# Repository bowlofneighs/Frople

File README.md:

# frople
Frople is a split ergonomic keyboard with a 40 key layout. It utilizes a 6x3 main matrix and a 2x1 thumbfan on each side. It uses 2 Arduino Pro Micros as its MCUs and QMK for the firmware. The keys were designed specifically with my hand dimensions in mind, seeing as I took measurements of my finger-length to decide the key stagger. It will take advantage of home-row-mods to allow me to still use my mod keys with such a small key footprint. It also has extra layers to account for the keys that could not fit on the main layer. It uses a TRS cable to communicate between the two halves of the keyboard using serial communcation. In the future it could theoretically be upgraded with a Nice!Nano V2 to allow for wireless communication between the two halves and the computer through BLE (bluetooth low energy). However my current computer does not have bluetooth and the Nice!Nano V2 was more expensive than the Arduino Pro Micro and as such I went with the Pro Micro for the MCU.

I built Frople because I have always been interested by those desktop setup videos, they seemed really cool, and I thought that a split keyboard would be a way to take my desk to the next level. I also made it because I tried out home-row-mods on my normal keyboard using a software called [Kanata](https://github.com/jtroo/kanata) and I found that it really increased my power-useriness and I wanted to take that to the next level. I also am really unsatisfied with my current keyboard, especially the lack of linux compatibal firmware. The final reason I wanted to make a split keyboard is because it sounded like a really fun project to get into hardware design with.

|Item                  |Description                  |Quantity                          |Unit Price CAD   |Unit Price USD|Price + tax * quantity (CAD)|Price + tax * quantity (USD)|Shipping CAD             |shipping USD|Note                                                  |Link                                                                                                                                                                                                                                                                                                                                                                                                                                                                                                                                                                                    |
|----------------------|-----------------------------|----------------------------------|-----------------|--------------|----------------------------|----------------------------|-------------------------|------------|------------------------------------------------------|----------------------------------------------------------------------------------------------------------------------------------------------------------------------------------------------------------------------------------------------------------------------------------------------------------------------------------------------------------------------------------------------------------------------------------------------------------------------------------------------------------------------------------------------------------------------------------------|
|Red Choc Switches     |Key Switches                 |40pcs                             |29.41 + 3.82(tax)|23.93USD      |33.23                       |23.93 USD                   |FREE                     |FREE        |                                                      |https://www.aliexpress.com/item/1005008751312031.html?algo_exp_id=cdb82bfe-653e-4ba2-895b-58cb39c5a6ad-1&pdp_ext_f=%7B%22order%22%3A%22150%22%2C%22eval%22%3A%221%22%2C%22fromPage%22%3A%22search%22%7D&utparam-url=scene%3Asearch%7Cquery_from%3A%7Cx_object_id%3A1005008751312031%7C_p_origin_prod%3A                                                                                                                                                                                                                                                                                 |
|Kailh Hot Swap sockets|Hot swaps                    |1 (they come in packs of 100 :hs:)|12.87 + 1.67(tax)|10.47 USD     |14.54                       |10.47 USD                   |FREE                     |FREE        |even though it was 100 they were still the cheapest   |https://www.aliexpress.com/item/1005006625852715.html?algo_exp_id=faa48a85-e9cd-40e5-93a0-2959f27b83d9-4&pdp_ext_f=%7B%22order%22%3A%22105%22%2C%22spu_best_type%22%3A%22order%22%2C%22eval%22%3A%221%22%2C%22fromPage%22%3A%22search%22%7D&utparam-url=scene%3Asearch%7Cquery_from%3A%7Cx_object_id%3A1005006625852715%7C_p_origin_prod%3A                                                                                                                                                                                                                                             |
|Arduino Pro Micro     |MCU                          |2                                 |8.99 + 1.16      |7.31 USD      |20.3                        |14.62 USD                   |FREE                     |FREE        |                                                      |https://www.aliexpress.com/item/1005008804370504.html?aem_p4p_detail=202601150944273562095180064590002000670&algo_exp_id=7d831326-f6b0-4daf-bc1d-06556968d806-7&pdp_ext_f=%7B%22order%22%3A%2229%22%2C%22eval%22%3A%221%22%2C%22fromPage%22%3A%22search%22%7D&utparam-url=scene%3Asearch%7Cquery_from%3A%7Cx_object_id%3A1005008804370504%7C_p_origin_prod%3A&search_p4p_id=202601150944273562095180064590002000670_2                                                                                                                                                                   |
|Keycaps               |choc low profile ldsa keycaps|4 they come in packs of 10        |5 + 0.65         |4.06 USD      |22.6                        |16.27 USD                   |10 + 1.3                 |8.13USD     |I couldn’t find cheaper unmarked keycaps on aliexpress|https://lowprokb.ca/collections/keycaps/products/ldsa-low-profile-blank-keycaps?variant=44790995878052                                                                                                                                                                                                                                                                                                                                                                                                                                                                                  |
|SJ1-3533NG            |TRS audio jack               |2                                 |3.15 + 0.40      |2.55 USD      |7.1                         |5.11 USD                    |5.54 + 0.72              |4.50 USD    |LCSC was much more expensive bc shipping              |https://www.aliexpress.com/item/1005007818050385.html?spm=a2g0o.productlist.main.2.428d1a0el9FCCd&algo_pvid=9e128295-691e-43e5-8a00-b08dc531eca2&algo_exp_id=9e128295-691e-43e5-8a00-b08dc531eca2-1&pdp_ext_f={%22order%22%3A%221%22%2C%22eval%22%3A%221%22%2C%22fromPage%22%3A%22search%22}&pdp_npi=6%40dis!CAD!3.15!3.15!!!15.45!15.45!%402101c44517685003345927398e8be0!12000042315760823!sea!CA!0!ABX!1!0!n_tag%3A-29910%3Bd%3A53760023%3Bm03_new_user%3A-29895&curPageLogUid=4tlGIj6PnRZU&utparam-url=scene%3Asearch&#124;query_from%3A&#124;x_object_id%3A1005007818050385&#124;_p_origin_prod%3A|
|PCB                   |keyboard pcb                 |1                                 |                 |19.00 USD     |                            |19.00 USD                   |                         |13.25 USD   |                                                      |https://hc-cdn.hel1.your-objectstorage.com/s/v3/6d1642395864fce0_image.png                                                                                                                                                                                                                                                                                                                                                                                                                                                                                                              |
|ec-11                 |rotary encoder               |1 They come in packs of 5         |1.62 + 0.21      |1.31 USD      |1.83                        |1.31 USD                    |FREE                     |FREE        |                                                      |https://www.aliexpress.com/item/1005003824684681.html?algo_exp_id=11db7878-987f-4212-a431-20684286fbad-2&pdp_ext_f=%7B%22order%22%3A%22289%22%2C%22spu_best_type%22%3A%22order%22%2C%22eval%22%3A%221%22%2C%22fromPage%22%3A%22search%22%7D&utparam-url=scene%3Asearch%7Cquery_from%3A%7Cx_object_id%3A1005003824684681%7C_p_origin_prod%3A                                                                                                                                                                                                                                             |
|                      |                             |                                  |                 |              |                            |                            |                         |            |                                                      |                                                                                                                                                                                                                                                                                                                                                                                                                                                                                                                                                                                        |
|Total                 |                             |                                  |                 |              |99.6 CAD (not including pcb)|90.71 USD                   |17.56 (Not including pcb)|25.88       |full cost:: 116.59 USD                                |                                                                                                                                                                                                                                                                                                                                                                                                                                                                                                                                                                                        |

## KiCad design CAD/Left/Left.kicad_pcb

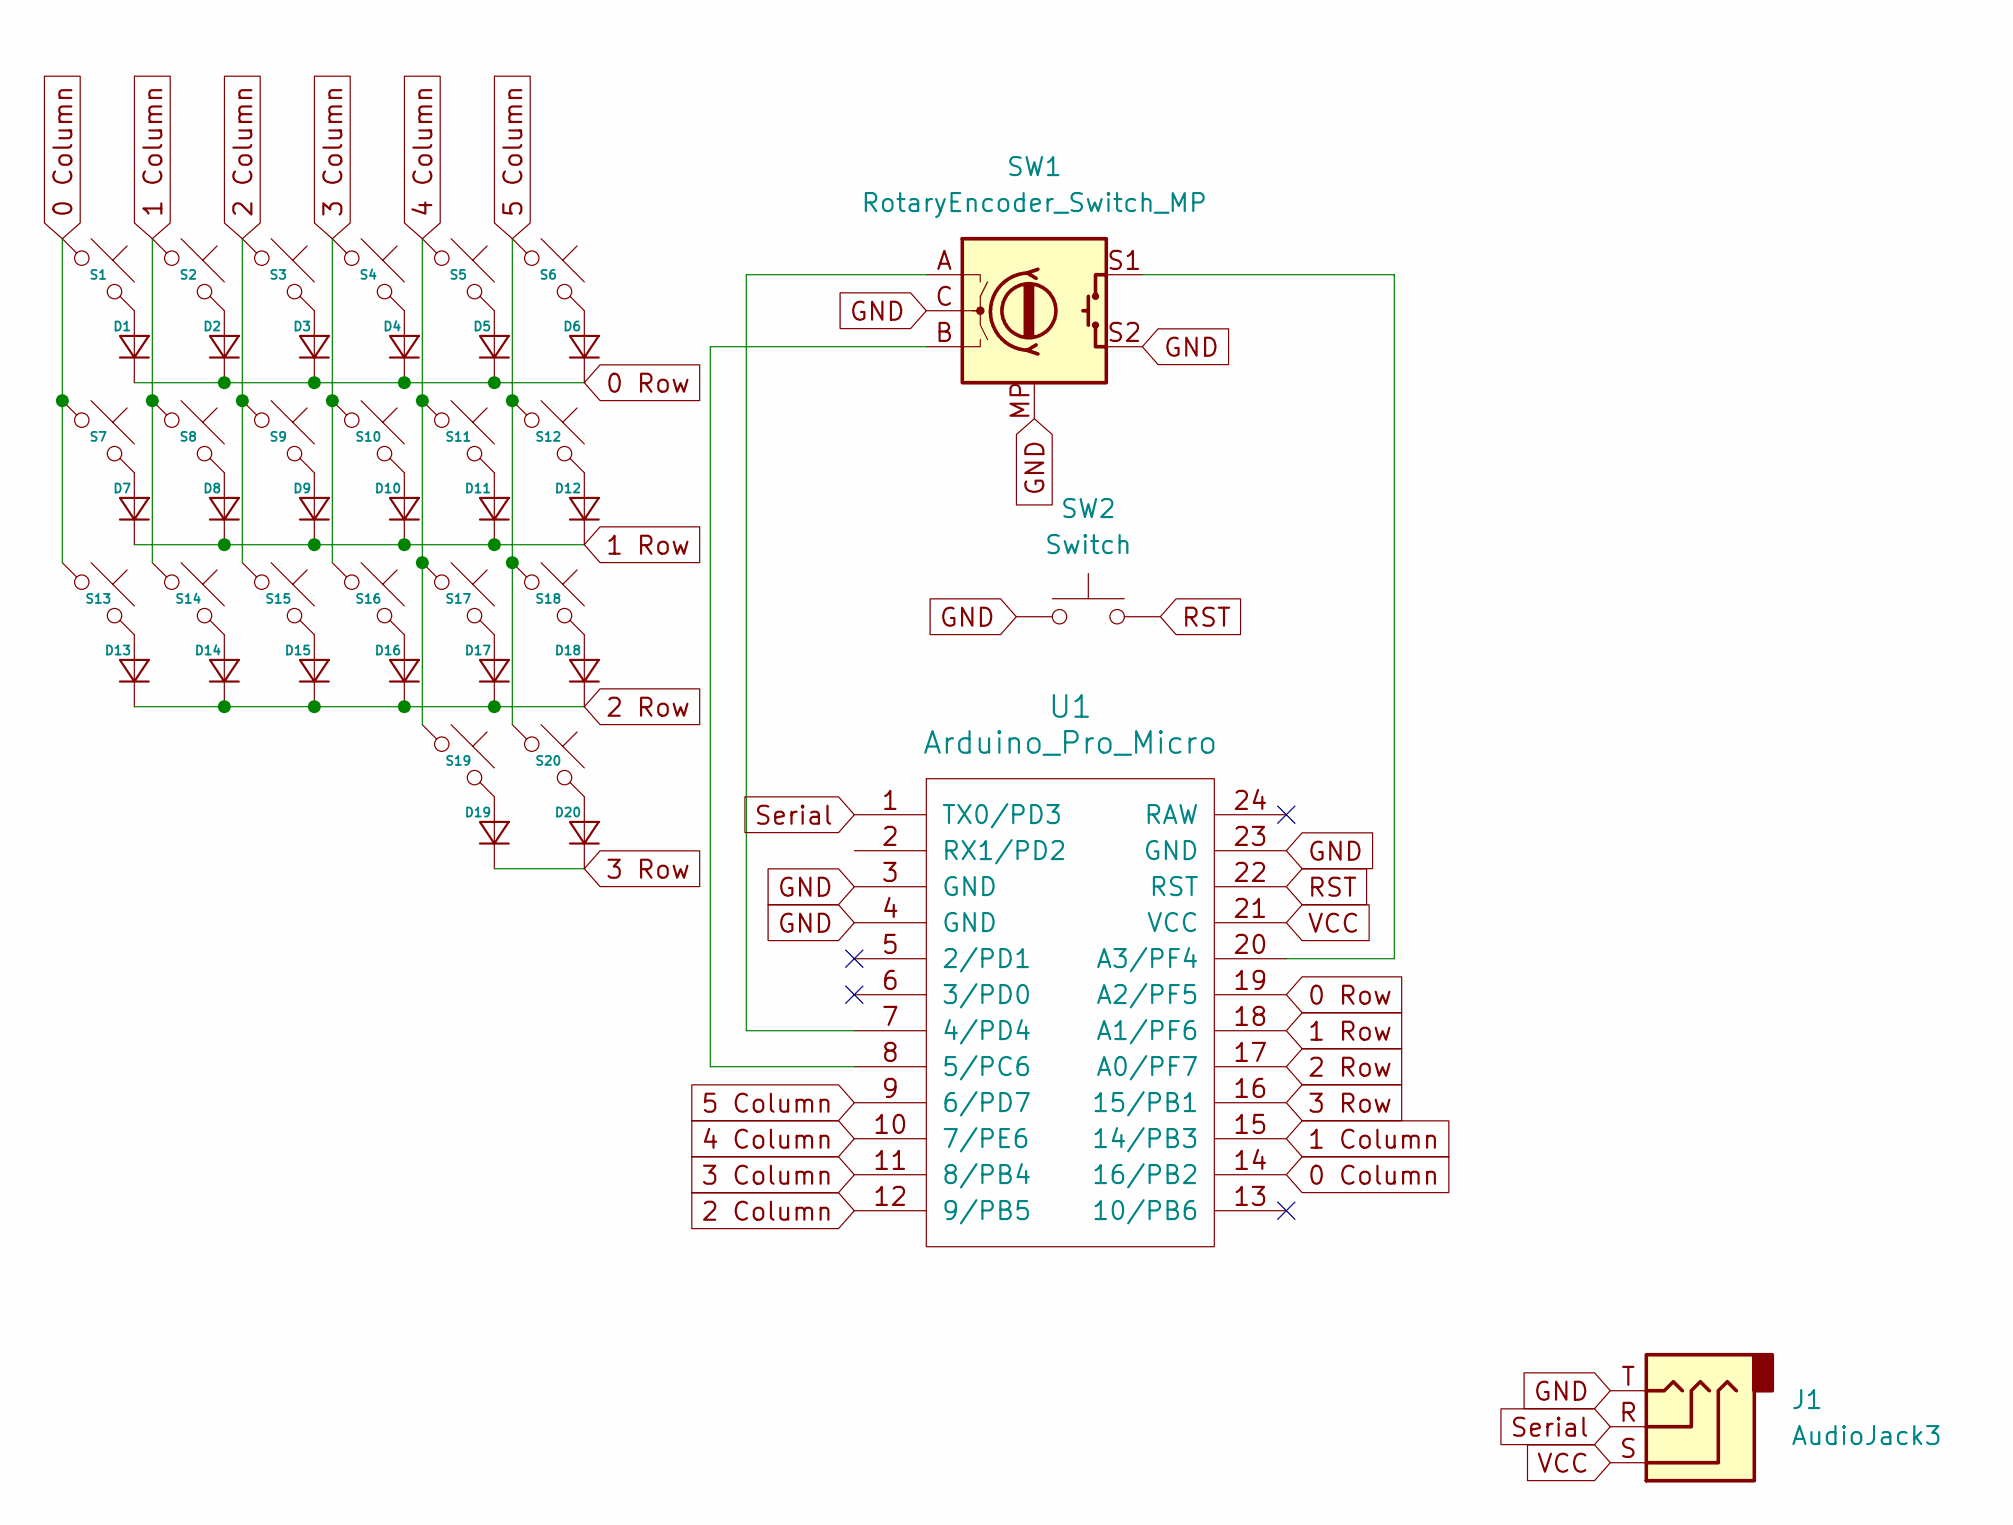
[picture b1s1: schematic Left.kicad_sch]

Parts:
D1, D2, D3, D4, D5, D6, D7, D8, D9, D10, D11, D12, D13, D14, D15, D16, D17, D18, D19, D20: D_SOD-123
J1: AudioJack3; Jack_3.5mm_CUI_SJ1-3533NG_Horizontal_CircularHoles
S1, S2, S3, S4, S5, S6, S7, S8, S9, S10, S11, S12, S13, S14, S15, S16, S17, S18, S19, S20: Hotswap_Choc_V1
SW1: RotaryEncoder_Switch_MP; RotaryEncoder_Alps_EC11E-Switch_Vertical_H20mm
SW2: Switch; Button_MJTP1243
U1: Arduino_Pro_Micro; Sparkfun_Pro_Micro

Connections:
0 Column: S1.1, S7.1, S13.1, U1.14 (16/PB2)
0 Row: D1.1 (K), D2.1 (K), D3.1 (K), D4.1 (K), D5.1 (K), D6.1 (K), U1.19 (A2/PF5)
1 Column: S2.1, S8.1, S14.1, U1.15 (14/PB3)
1 Row: D7.1 (K), D8.1 (K), D9.1 (K), D10.1 (K), D11.1 (K), D12.1 (K), U1.18 (A1/PF6)
2 Column: S3.1, S9.1, S15.1, U1.12 (9/PB5)
2 Row: D13.1 (K), D14.1 (K), D15.1 (K), D16.1 (K), D17.1 (K), D18.1 (K), U1.17 (A0/PF7)
3 Column: S4.1, S10.1, S16.1, U1.11 (8/PB4)
3 Row: D19.1 (K), D20.1 (K), U1.16 (15/PB1)
4 Column: S5.1, S11.1, S17.1, S19.1, U1.10 (7/PE6)
5 Column: S6.1, S12.1, S18.1, S20.1, U1.9 (6/PD7)
GND: J1.T, SW1.C, SW1.MP, SW1.S2, SW2.1, U1.3 (GND), U1.4 (GND), U1.23 (GND)
unnamed: D1.2 (A), S1.2
unnamed: D2.2 (A), S2.2
unnamed: D3.2 (A), S3.2
unnamed: D4.2 (A), S4.2
unnamed: D5.2 (A), S5.2
unnamed: D6.2 (A), S6.2
unnamed: D7.2 (A), S7.2
unnamed: D8.2 (A), S8.2
unnamed: D9.2 (A), S9.2
unnamed: D10.2 (A), S10.2
unnamed: D11.2 (A), S11.2
unnamed: D12.2 (A), S12.2
unnamed: D13.2 (A), S13.2
unnamed: D14.2 (A), S14.2
unnamed: D15.2 (A), S15.2
unnamed: D16.2 (A), S16.2
unnamed: D17.2 (A), S17.2
unnamed: D18.2 (A), S18.2
unnamed: D19.2 (A), S19.2
unnamed: D20.2 (A), S20.2
unnamed: SW1.A, U1.7 (4/PD4)
unnamed: SW1.B, U1.8 (5/PC6)
unnamed: SW1.S1, U1.20 (A3/PF4)
RST: SW2.2, U1.22 (RST)
Serial: J1.R, U1.1 (TX0/PD3)
VCC: J1.S, U1.21 (VCC)

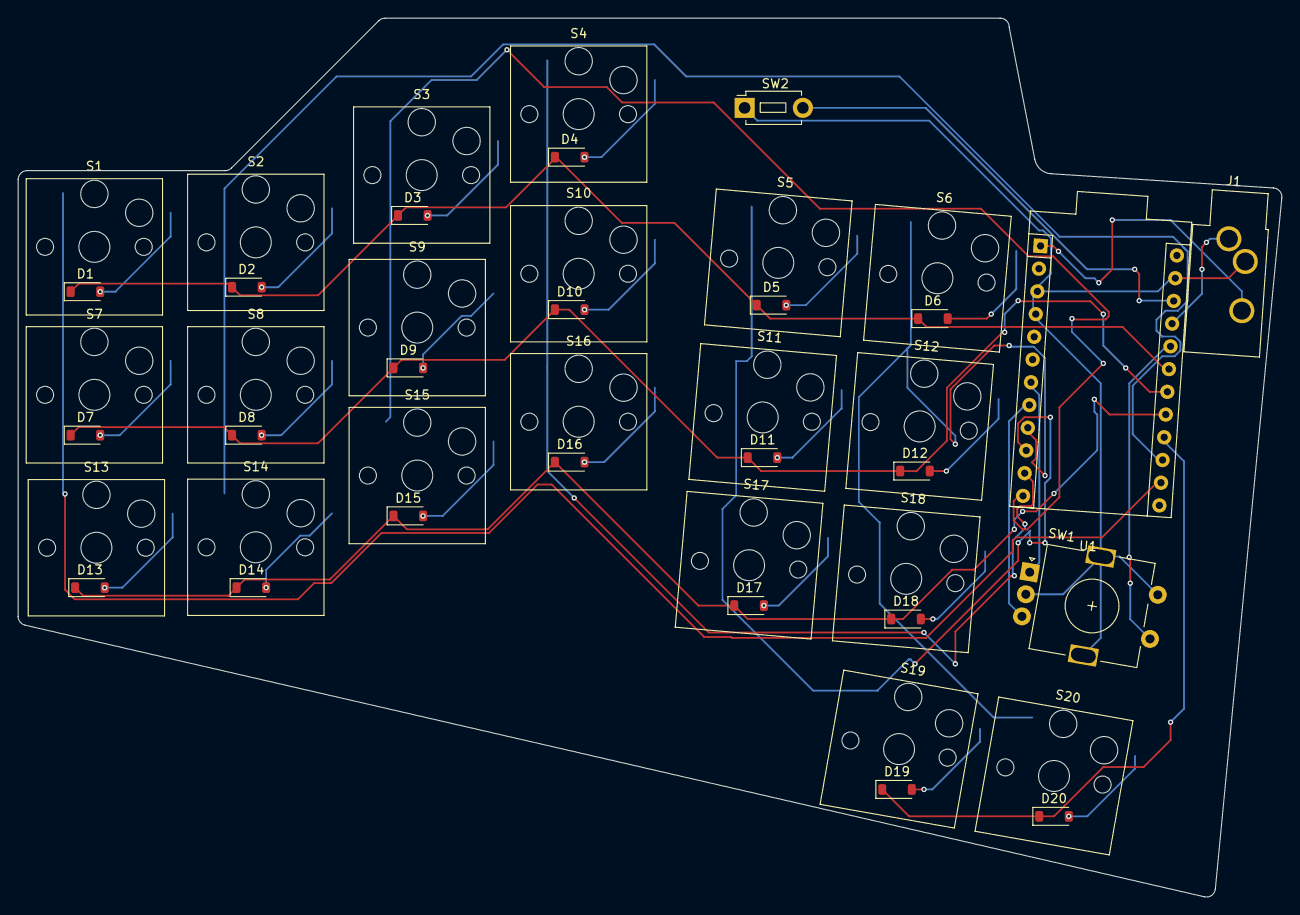
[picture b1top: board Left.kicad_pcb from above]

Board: 2 copper layers, 140.9 x 98.0 mm, 44 parts (0 on the bottom side), 37 nets.

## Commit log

2025-10-16 added main.yaml and raw.svg
2025-10-16 added pcb.kicad_pcb, updated yaml to include pcb and footprints finalized key layout
2025-10-16 updated readme to be the same as what is on the Blueprint website
2025-10-17 begun creation of schematic, probably willl have to overhaul pcb
2025-10-17 cleaned stuff up, going to start pcb from scratch
2025-10-26 made the pcbs
2025-12-15 deleted: Productionforrealzthistime (2).zip deleted: kicad-lib-arduino deleted: scottokeebs
2025-12-15 about halfway done left pcb
2025-12-15 figured out footprints and stuff
2025-12-15 finished left PCB
2025-12-16 begun work on right PCB, mainly just copying the left one while flipping/rotating a couple things
2025-12-16 fixed previous commit
2025-12-28 changed from I2C communication between the halves to serial because it's easier with QMK
2026-01-15 added firmware
2026-01-15 restructured files
2026-01-15 created gerbers
2026-01-15 finished please
2026-01-15 revised bom
2026-02-05 Revise README with detailed Frople keyboard description
    Updated the README to provide a detailed description of the Frople keyboard, including its layout, components, and future upgrade possibilities.
2026-02-05 Update README with component details and pricing
    Added detailed specifications and pricing for keyboard components.
2026-02-05 Expand README with personal motivation for Frople
    Added a personal motivation section for building Frople.
2026-02-05 finalized BOM.csv
2026-02-12 added image for the readme
2026-02-12 Update README with image and item table
    Added an image render and a table for item descriptions.
2026-02-12 Add image and enhance README formatting
    Updated README to include an image and improve formatting.
2026-02-12 Enhance README with Frople keyboard details
    Added a brief introduction and features of the Frople keyboard.
